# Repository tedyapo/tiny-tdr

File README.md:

# tiny-tdr
Time-domain reflectometery add-on for your oscilloscope

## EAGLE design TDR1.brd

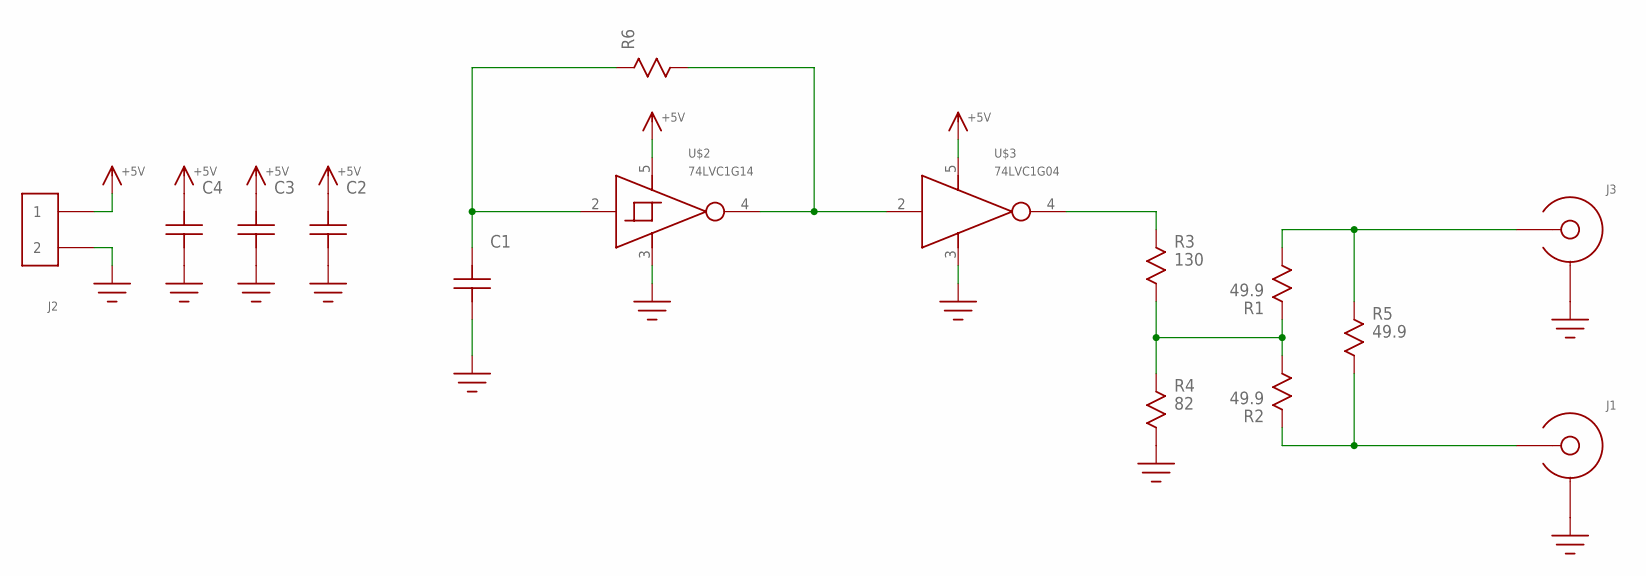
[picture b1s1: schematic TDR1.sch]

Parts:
C1, C2, C3: C0603
C4: C1206; 1206
J1: BNC_MALE_PCB
J2: HEADER_2PIN
J3: EDGE_LAUNCH_JACK; EDGE_LAUNCH_RF_CON
R1, R2, R5: 49.9; R0603
R3: 130; R0603
R4: 82; R0603
R6: R0603
U$2: 74LVC1G14; SOT23-5
U$3: 74LVC1G04; SOT23-5

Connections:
+5V: C2.P$2, C3.P$2, C4.P$2, J2.1, U$2.5 (VCC), U$3.5 (VCC)
GND: C1.P$1, C2.P$1, C3.P$1, C4.P$1, J1.SHIELD@1 (SHIELD), J1.SHIELD@2 (SHIELD), J1.SHIELD@3 (SHIELD), J1.SHIELD@4 (SHIELD), J2.2, J3.GND@1 (SHIELD), J3.GND@2 (SHIELD), J3.GND@3 (SHIELD), J3.GND@4 (SHIELD), J3.GND@5 (SHIELD), J3.GND@6 (SHIELD), J3.GND@7 (SHIELD), J3.GND@8 (SHIELD), J3.GND@9 (SHIELD), J3.GND@10 (SHIELD), J3.GND@11 (SHIELD), J3.GND@12 (SHIELD), J3.SHIELD@1 (SHIELD), J3.SHIELD@2 (SHIELD), R4.P$2, U$2.3 (GND), U$3.3 (GND)
unnamed: C1.P$2, R6.P$1, U$2.2 (IN)
unnamed: R6.P$2, U$2.4 (OUT), U$3.2 (IN)
unnamed: R1.P$1, R2.P$2, R3.P$2, R4.P$1
unnamed: R3.P$1, U$3.4 (OUT)
unnamed: J3.CENTER, R1.P$2, R5.P$1
unnamed: J1.CENTER, R2.P$1, R5.P$2

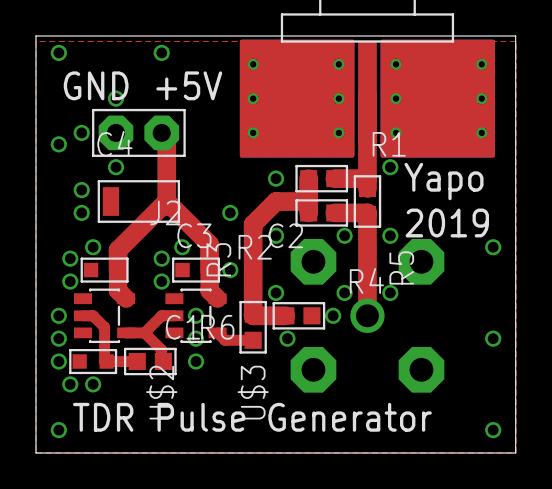
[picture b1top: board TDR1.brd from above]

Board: 2 copper layers, 26.6 x 23.2 mm, 15 parts (0 on the bottom side), 8 nets.

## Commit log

2019-03-01 now with files!
